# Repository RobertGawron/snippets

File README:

Projects from my blog ( http://robertgawron.blogspot.com/ ).

Visit README in project directory for description and link to an article.

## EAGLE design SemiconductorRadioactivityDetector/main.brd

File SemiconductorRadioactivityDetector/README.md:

Current version located here:

https://github.com/RobertGawron/SemiconductorRadioactivityDetector

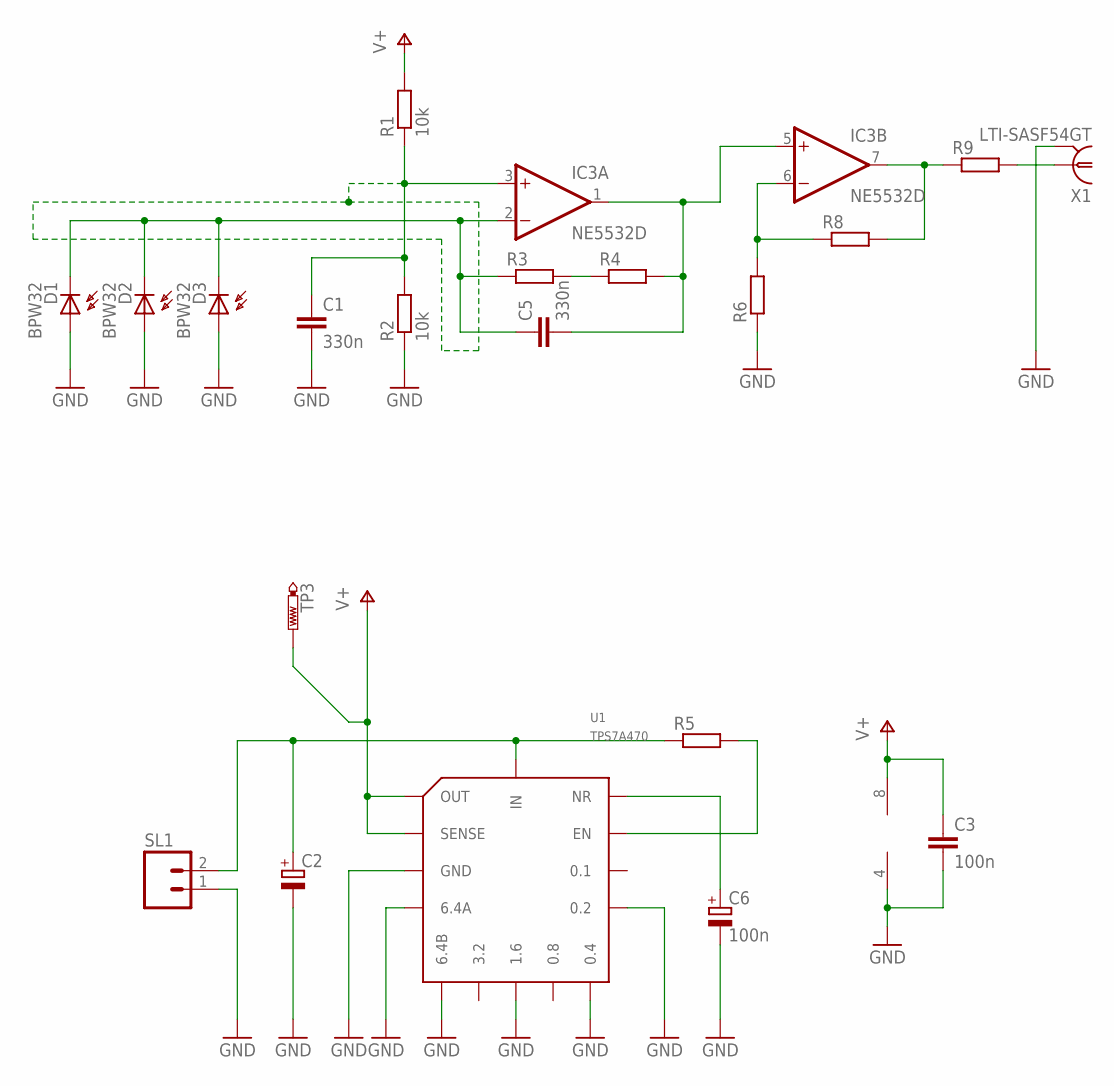
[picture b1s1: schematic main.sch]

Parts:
C1, C5: 330n; C0805
C2: CPOL-EUT/3528-12R; T/3528-12R
C3: 100n; C0805
C6: 100n; A/3216-18W
D1, D2, D3: BPW32
IC3: NE5532D; SO08
R1, R2: 10k; R0805
R3, R4: R-EU_MELF0204W; MINI_MELF-0204W
R5: R-EU_M1206; M1206
R6, R9: R-EU_0204/2V; 0204V
R8: R-EU_M0805; M0805
SL1: M02; 02P
TP3: PTR1TP12R; TP12R
U1: TPS7A470; S-PVQFN-N20
X1: LTI-SASF54GT

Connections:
GND: C1.2, C2.-, C3.2, C6.-, D1.A, D2.A, D3.A, IC3.4 (V-), R2.1, R6.1, SL1.1, U1.2 (GND), U1.4 (6.4A), U1.5 (6.4B), U1.7 (GND), U1.8 (1.6), U1.10 (0.4), U1.11 (0.2), U1.17 (GND), U1.18 (GND), U1.19 (GND), U1.EXP (GND), X1.2, X1.3 (2), X1.4 (2), X1.5 (2)
unnamed: C5.2, IC3.1 (OUT), IC3.5 (+IN), R4.2
unnamed: IC3.6 (-IN), R6.2, R8.1
unnamed: R3.2, R4.1
unnamed: C5.1, D1.K (C), D2.K (C), D3.K (C), IC3.2 (-IN), R3.1
unnamed: C6.+, U1.14 (NR)
unnamed: R5.2, U1.13 (EN)
unnamed: C2.+, R5.1, SL1.2, U1.15 (IN), U1.16 (IN)
unnamed: IC3.7 (OUT), R8.2, R9.1
unnamed: C1.1, IC3.3 (+IN), R1.1, R2.2
unnamed: R9.2, X1.1
V+: C3.1, IC3.8 (V+), R1.2, TP3.TP, U1.1 (OUT), U1.3 (SENSE), U1.20 (OUT)

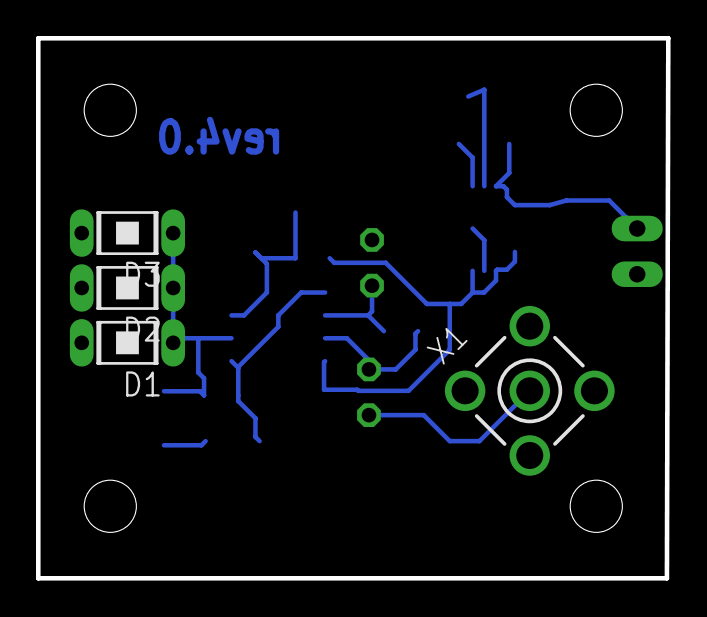
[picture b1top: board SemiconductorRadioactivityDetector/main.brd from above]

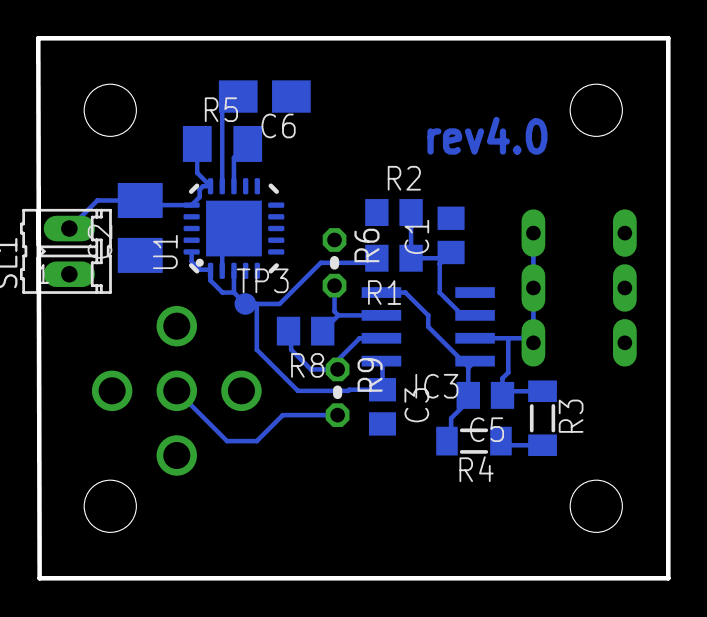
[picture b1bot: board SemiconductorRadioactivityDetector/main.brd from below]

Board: 2 copper layers, 35.0 x 30.0 mm, 21 parts (17 on the bottom side), 12 nets.

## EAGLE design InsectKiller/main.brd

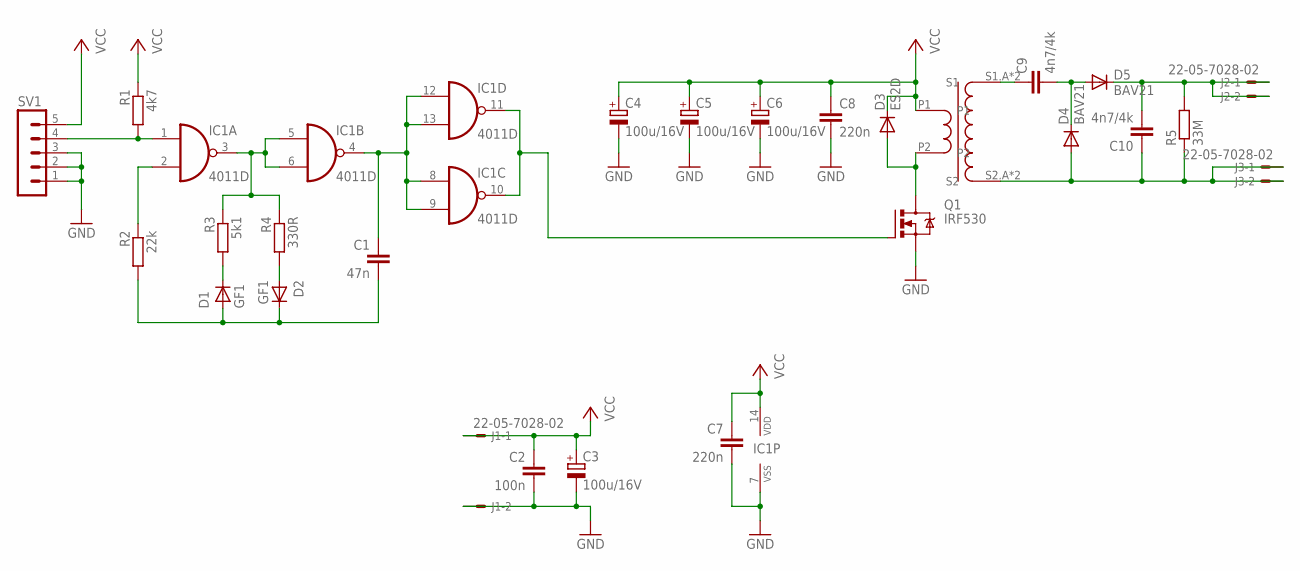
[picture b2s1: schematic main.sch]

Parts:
11: CCFL_INVERTER_COIL
C1: 47n; C025-025X050
C2: 100n; C0805
C3, C4, C5, C6: 100u/16V; 153CLV-0505
C7, C8: 220n; C0805
C9, C10: 4n7/4k; C075-042X103
D1, D2: GF1; SMA-DO214AC
D3: ES2D; SMB
D4, D5: BAV21; DO35-10
IC1: 4011D; SO14
J1, J2, J3: 22-05-7028-02; 7395-02
Q1: IRF530; TO220BV
R1: 4k7; M0805
R2: 22k; M0805
R3: 5k1; M0805
R4: 330R; M0805
R5: 33M; 0207/10
SV1: MA05-1

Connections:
GND: C2.2, C3.-, C4.-, C5.-, C6.-, C7.2, C8.2, IC1.7 (VSS), J1.2, Q1.S, SV1.1, SV1.2, SV1.3
unnamed: IC1.2 (I1), R2.1
unnamed: IC1.1 (I0), R1.2, SV1.4
unnamed: 11.P2, D3.A, Q1.D
unnamed: IC1.10 (O), IC1.11 (O), Q1.G
unnamed: C1.1, IC1.4 (O), IC1.8 (I0), IC1.9 (I1), IC1.12 (I0), IC1.13 (I1)
unnamed: 11.S1.A (S1), 11.S1.B (S1), C9.1
unnamed: C9.2, D4.C, D5.A
unnamed: C10.2, D5.C, J2.1, J2.2, R5.2
unnamed: 11.S2.A (S2), 11.S2.B (S2), C10.1, D4.A, J3.1, J3.2, R5.1
unnamed: IC1.3 (O), IC1.5 (I0), IC1.6 (I1), R3.1, R4.1
unnamed: C1.2, D1.A, D2.K (C), R2.2
unnamed: D1.K (C), R3.2
unnamed: D2.A, R4.2
VCC: 11.P1, C2.1, C3.+, C4.+, C5.+, C6.+, C7.1, C8.1, D3.C, IC1.14 (VDD), J1.1, R1.1, SV1.5

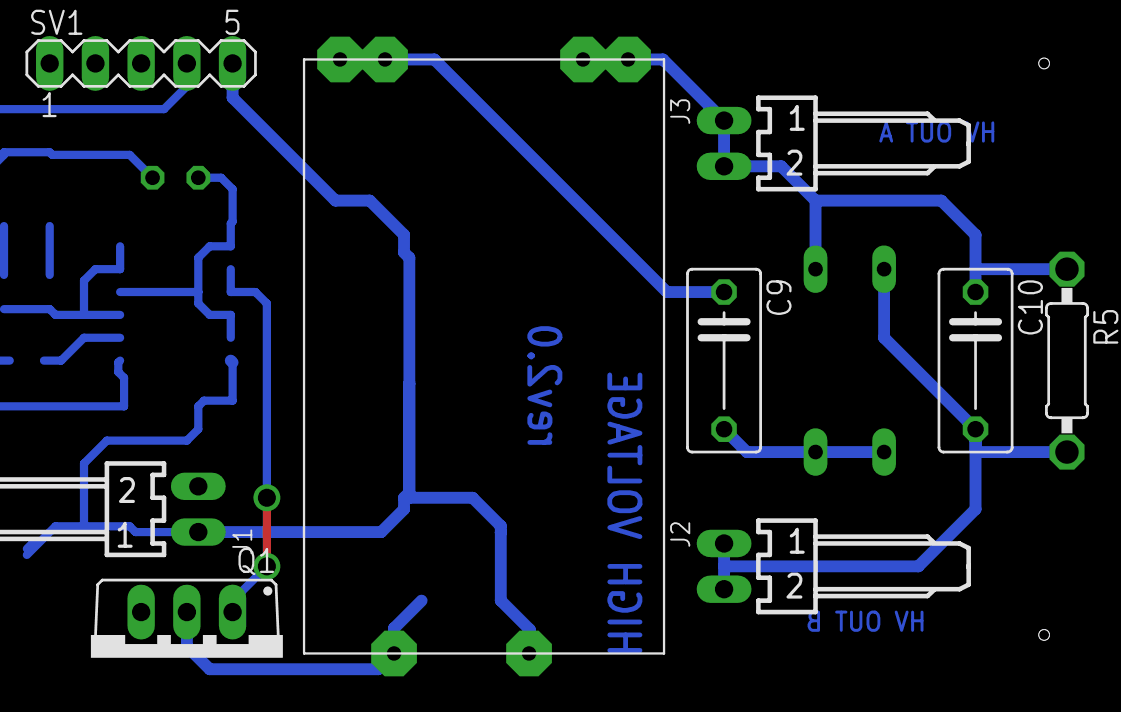
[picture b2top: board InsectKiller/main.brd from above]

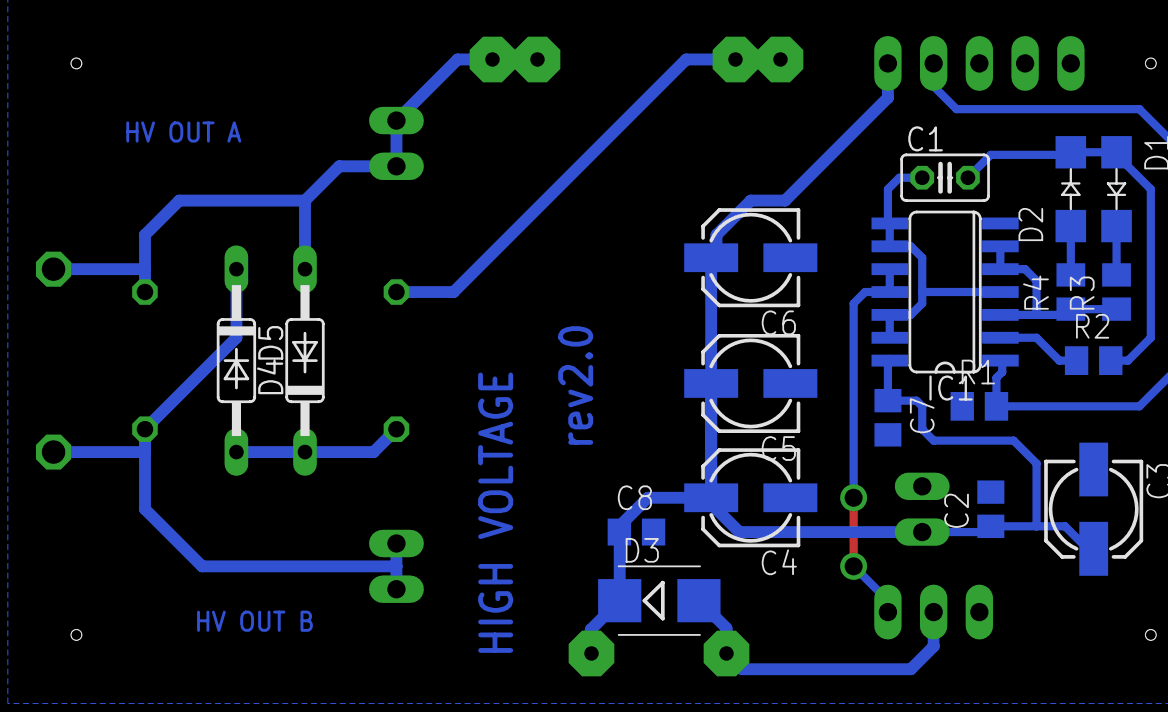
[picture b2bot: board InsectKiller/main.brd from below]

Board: 2 copper layers, 27 parts (18 on the bottom side), 15 nets.

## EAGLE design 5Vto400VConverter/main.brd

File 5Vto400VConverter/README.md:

# A small and cheap 5V/400V DC/DC converter.

For more info please visit full article:
http://robertgawron.blogspot.com/2016/03/5v400v-dcdc-converter.html

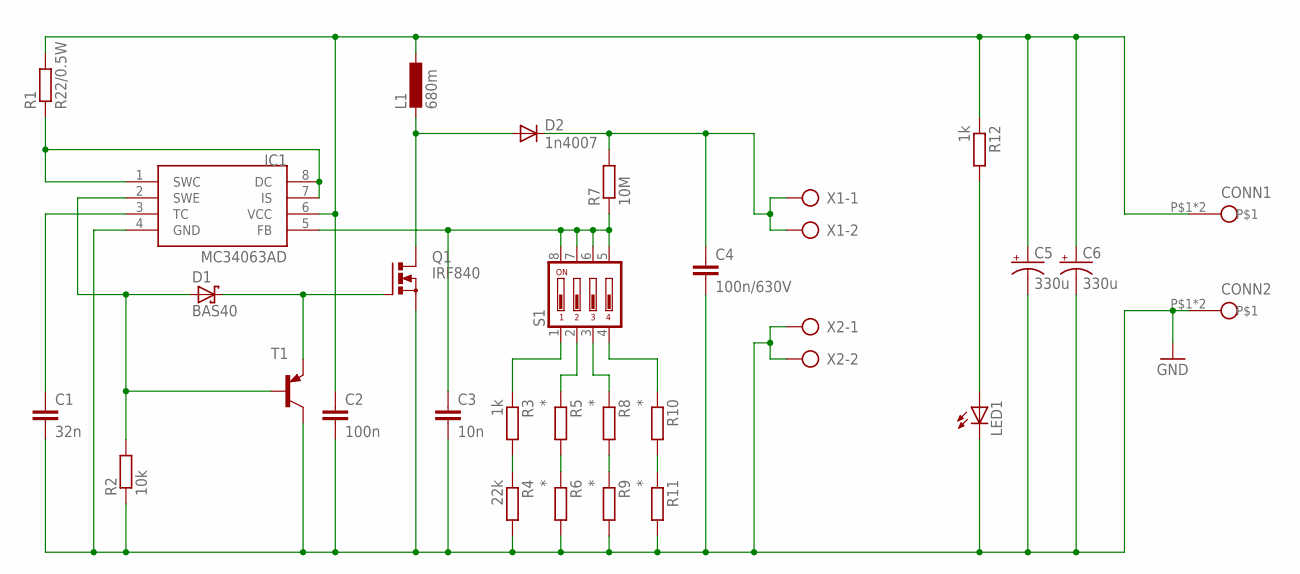
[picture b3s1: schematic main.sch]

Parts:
11, 12: BANANA-PLUG-2-PADS
C1: 32n; C025-025X050
C2: 100n; C3216
C3: 10n; C3216
C4: 100n/630V; C102-064X133
C5, C6: 330u; A/3216-18W
D1: BAS40; SOT23
D2: 1n4007; DO41-10
IC1: MC34063AD; SOIC8
L1: 680m; 0207/5V
LED1: LED3MM
Q1: IRF840; TO220BV
R1: R22/0.5W; 0207/5V
R2: 10k; R1206
R3, R12: 1k; R1206
R4: 22k; R1206
R5, R6, R8, R9, R10, R11: *; R1206
R7: 10M; 0207/5V
S1: DS04; DS-04
T1: BC807-40-PNP-SOT23-BEC; SOT23-BEC
X1, X2: AK500/2-H

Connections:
GND: 12.P$1, 12.P$2, C1.2, C2.2, C3.2, C4.2, C5.-, C6.-, IC1.4 (GND), LED1.K (C), Q1.S, R2.1, R4.2, R6.2, R9.2, R11.2, T1.C, X2.1, X2.2
unnamed: R8.2, R9.1
unnamed: R5.2, R6.1
unnamed: R3.2, R4.1
unnamed: R10.2, R11.1
unnamed: C1.1, IC1.3 (TC)
unnamed: R3.1, S1.1
unnamed: R5.1, S1.2
unnamed: R8.1, S1.3
unnamed: R10.1, S1.4
unnamed: LED1.A, R12.2
unnamed: IC1.1 (SWC), IC1.7 (IS), IC1.8 (DC), R1.1
unnamed: C3.1, IC1.5 (FB), R7.1, S1.5, S1.6, S1.7, S1.8
unnamed: D1.1 (A), IC1.2 (SWE), R2.2, T1.B
unnamed: D2.A, L1.2, Q1.D
unnamed: D1.3 (C), Q1.G, T1.E
unnamed: C4.1, D2.C, R7.2, X1.1, X1.2
VCC: 11.P$1, 11.P$2, C2.1, C5.+, C6.+, IC1.6 (VCC), L1.1, R1.2, R12.1

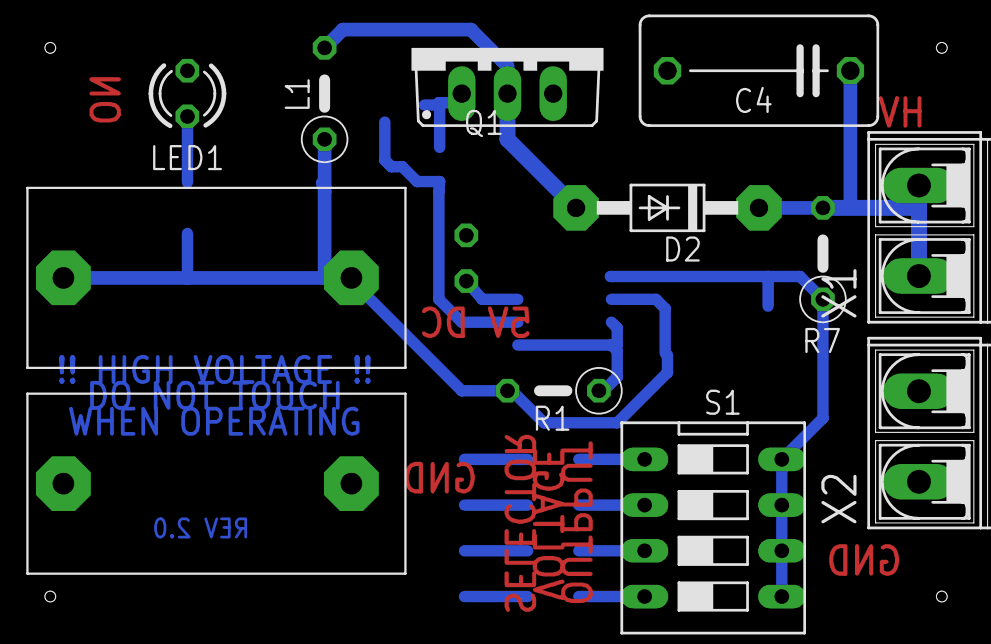
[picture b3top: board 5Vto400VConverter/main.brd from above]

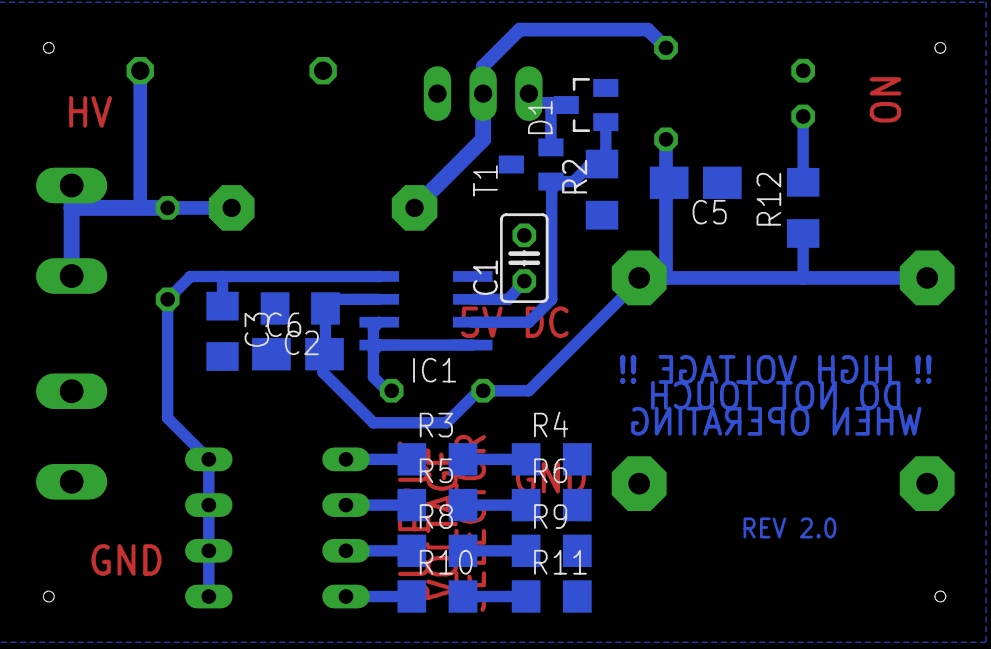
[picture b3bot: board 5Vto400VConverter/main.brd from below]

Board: 2 copper layers, 30 parts (18 on the bottom side), 18 nets.

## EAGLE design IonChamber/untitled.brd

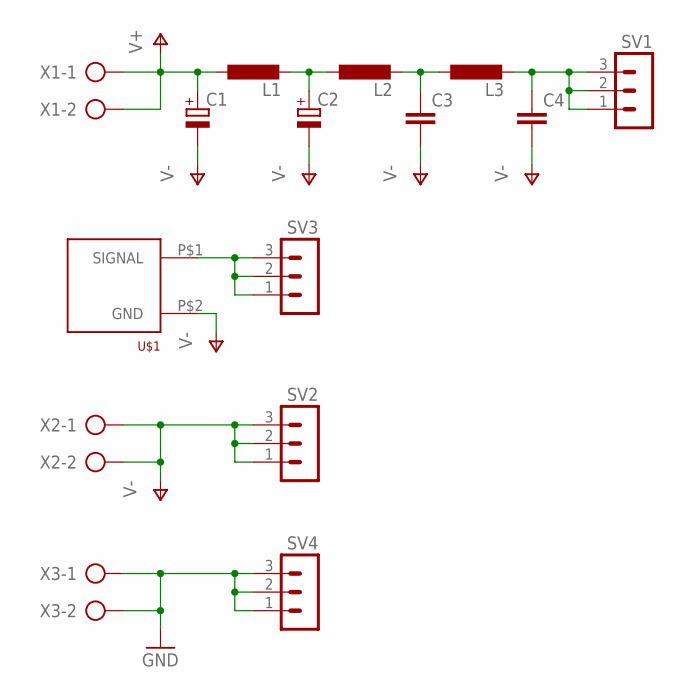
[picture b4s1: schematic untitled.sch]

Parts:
C1, C2: CPOL-EUSMCA; SMC_A
C3, C4: C-EUC1206; C1206
L1: L-EU0204/7; 0204/7
L2, L3: L-EUL1812; L1812
SV1, SV2, SV3, SV4: MA03-1
U$1: BNC_VERTICAL
X1, X2, X3: AK500/2-H

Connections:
GND: SV4.1, SV4.2, SV4.3, X3.1, X3.2
unnamed: C4.1, L3.2, SV1.1, SV1.2, SV1.3
unnamed: C2.+, L1.2, L2.1
unnamed: SV3.1, SV3.2, SV3.3, U$1.P$1 (SIGNAL)
unnamed: C3.1, L2.2, L3.1
V+: C1.+, L1.1, X1.1, X1.2
V-: C1.-, C2.-, C3.2, C4.2, SV2.1, SV2.2, SV2.3, U$1.P$2 (GND), X2.1, X2.2

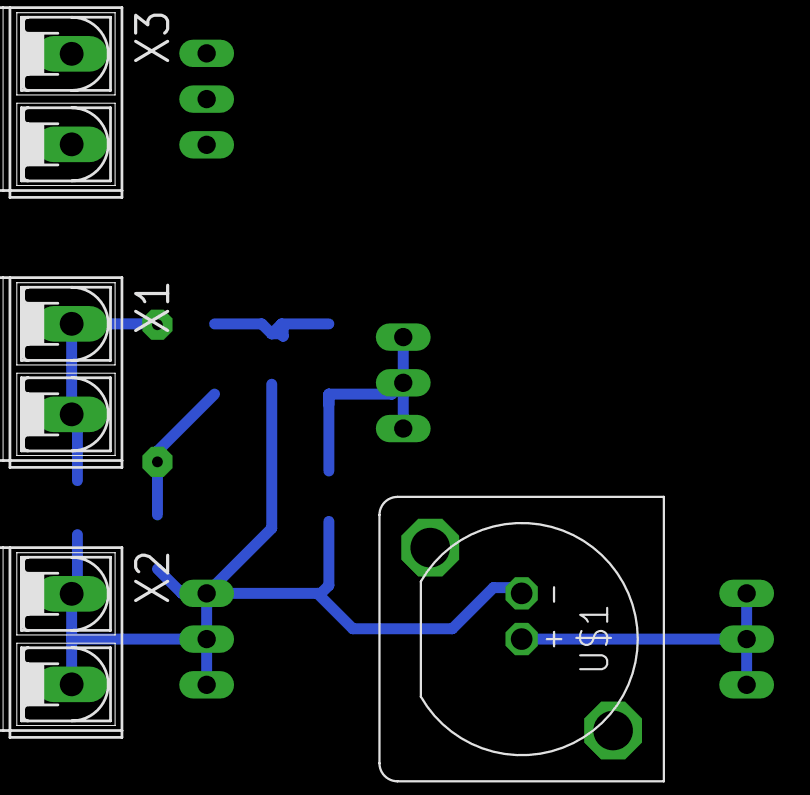
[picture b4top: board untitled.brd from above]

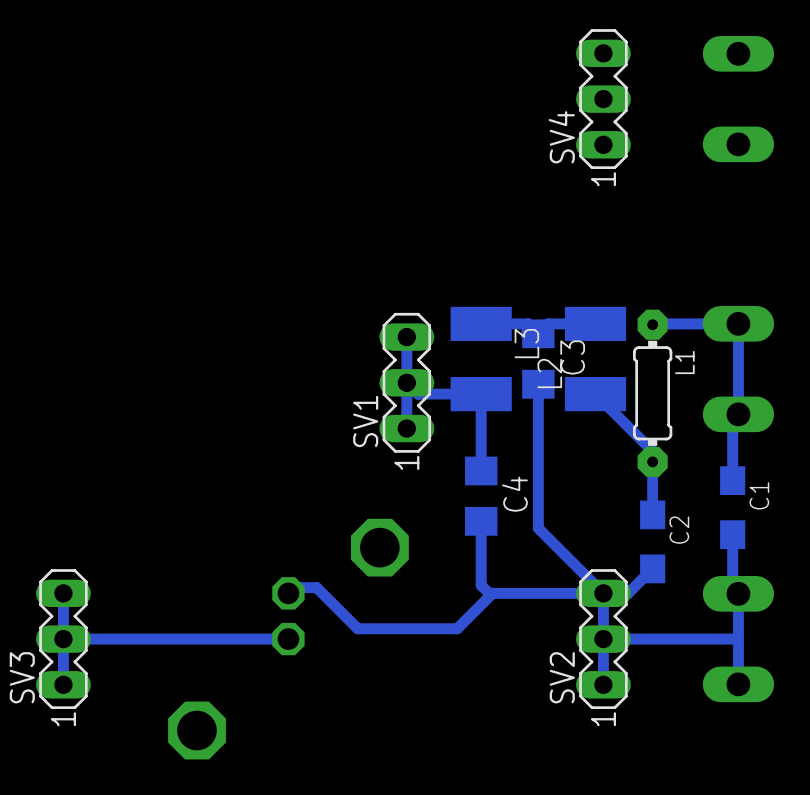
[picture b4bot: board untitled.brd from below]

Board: 2 copper layers, 15 parts (11 on the bottom side), 7 nets.

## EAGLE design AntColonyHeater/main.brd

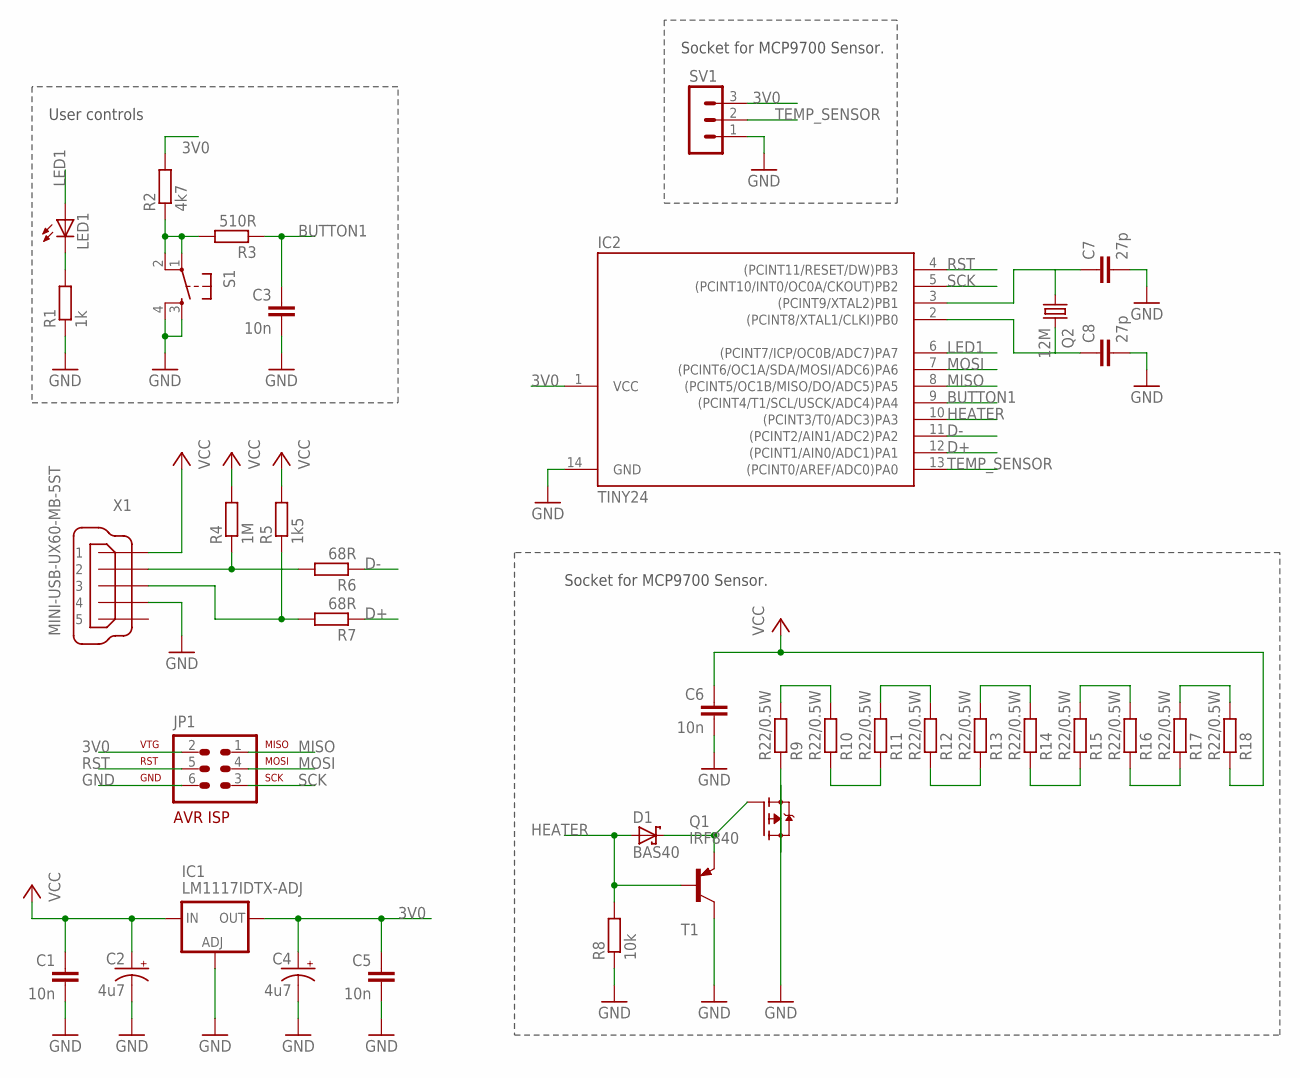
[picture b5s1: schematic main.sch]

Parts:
C1, C3, C5, C6: 10n; C1206
C2, C4: 4u7; A/3216-18W
C7, C8: 27p; C025-024X044
D1: BAS40; SOT23
IC1: LM1117IDTX-ADJ; TO252
IC2: TINY24; DIL14
JP1: AVR-ISP-6
LED1: LEDCHIP-LED0805; CHIP-LED0805
Q1: IRF840; TO252
Q2: 12M; HC18U-V
R1: 1k; R1206
R2: 4k7; R1206
R3: 510R; R1206
R4: 1M; R1206
R5: 1k5; R1206
R6, R7: 68R; R1206
R8: 10k; R1206
R9, R10, R11, R12, R13, R14, R15, R16, R17, R18: R22/0.5W; 0207/12
S1: TAC_SWITCHPTH; TACTILE-PTH
SV1: MA03-1
T1: BC807-40-PNP-SOT23-BEC; SOT23-BEC
X1: MINI-USB-UX60-MB-5ST; UX60-MB-5ST

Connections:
3V0: C4.+, C5.1, IC1.TAB (OUT), IC2.1 (VCC), JP1.2, R2.2, SV1.3
BUTTON1: C3.1, IC2.9 ((PCINT4/T1/SCL/USCK/ADC4)PA4), R3.1
D+: IC2.12 ((PCINT1/AIN0/ADC1)PA1), R7.1
D-: IC2.11 ((PCINT2/AIN1/ADC2)PA2), R6.1
GND: C1.2, C2.-, C3.2, C4.-, C5.2, C6.2, C7.2, C8.2, IC1.1 (ADJ), IC2.14 (GND), JP1.6, Q1.2 (S), R1.1, R8.1, S1.3, S1.4, SV1.1, T1.C, X1.4
HEATER: D1.1 (A), IC2.10 ((PCINT3/T0/ADC3)PA3), R8.2, T1.B
LED1: IC2.6 ((PCINT7/ICP/OC0B/ADC7)PA7), LED1.A
MISO: IC2.8 ((PCINT5/OC1B/MISO/DO/ADC5)PA5), JP1.1
MOSI: IC2.7 ((PCINT6/OC1A/SDA/MOSI/ADC6)PA6), JP1.4
unnamed: R4.1, R6.2, X1.2
unnamed: Q1.3 (D), R9.1
unnamed: R5.1, R7.2, X1.3
unnamed: C7.1, IC2.3 ((PCINT9/XTAL2)PB1), Q2.1
unnamed: R9.2, R10.2
unnamed: R2.1, R3.2, S1.1, S1.2
unnamed: R10.1, R11.1
unnamed: R11.2, R12.2
unnamed: R12.1, R13.1
unnamed: R13.2, R14.2
unnamed: R14.1, R15.1
unnamed: R15.2, R16.2
unnamed: R16.1, R17.1
unnamed: LED1.C, R1.2
unnamed: D1.3 (C), Q1.1 (G), T1.E
unnamed: R17.2, R18.2
PB0: C8.1, IC2.2 ((PCINT8/XTAL1/CLKI)PB0), Q2.2
RST: IC2.4 ((PCINT11/RESET/DW)PB3), JP1.5
SCK: IC2.5 ((PCINT10/INT0/OC0A/CKOUT)PB2), JP1.3
TEMP_SENSOR: IC2.13 ((PCINT0/AREF/ADC0)PA0), SV1.2
VCC: C1.1, C2.+, C6.1, IC1.2 (IN), R4.2, R5.2, R18.1, X1.1

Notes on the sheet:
Socket for MCP9700 Sensor.
User controls

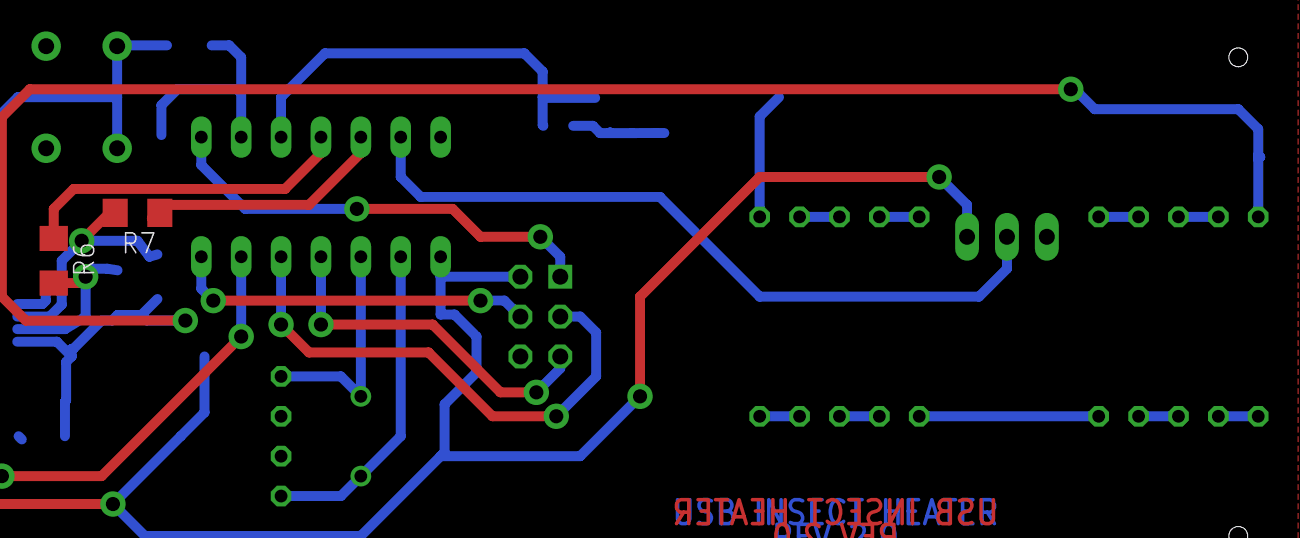
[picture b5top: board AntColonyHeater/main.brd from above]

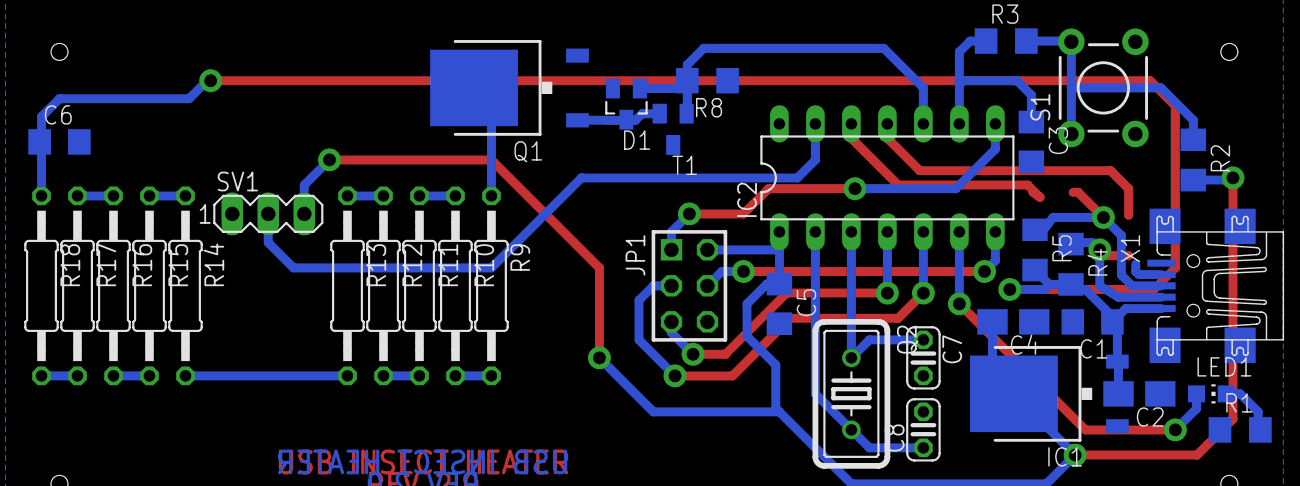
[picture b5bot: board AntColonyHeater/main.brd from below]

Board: 2 copper layers, 37 parts (35 on the bottom side), 30 nets.

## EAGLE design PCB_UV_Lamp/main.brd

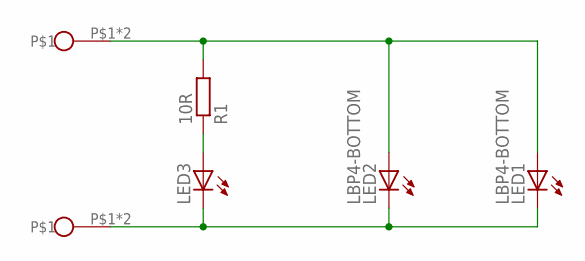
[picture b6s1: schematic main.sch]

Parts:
GND: BANANA-PLUG-2-PADS
LED1, LED2: LBP4-BOTTOM; P47F-BOTTOM
LED3: LED3MM
R1: 10R; R1206
U$1: BANANA-PLUG-2-PADS

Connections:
GND: LED1.A, LED2.A, R1.2, U$1.P$1, U$1.P$2
unnamed: GND.P$1, GND.P$2, LED1.C, LED2.C, LED3.K (C)
unnamed: LED3.A, R1.1

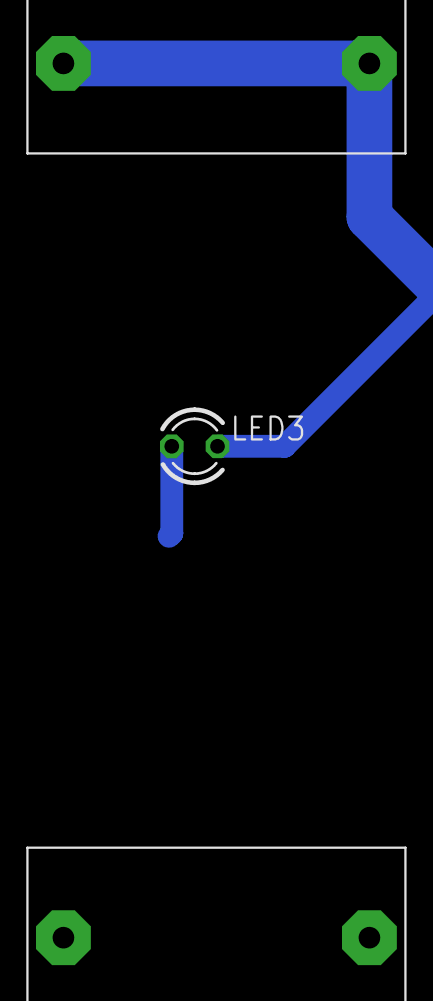
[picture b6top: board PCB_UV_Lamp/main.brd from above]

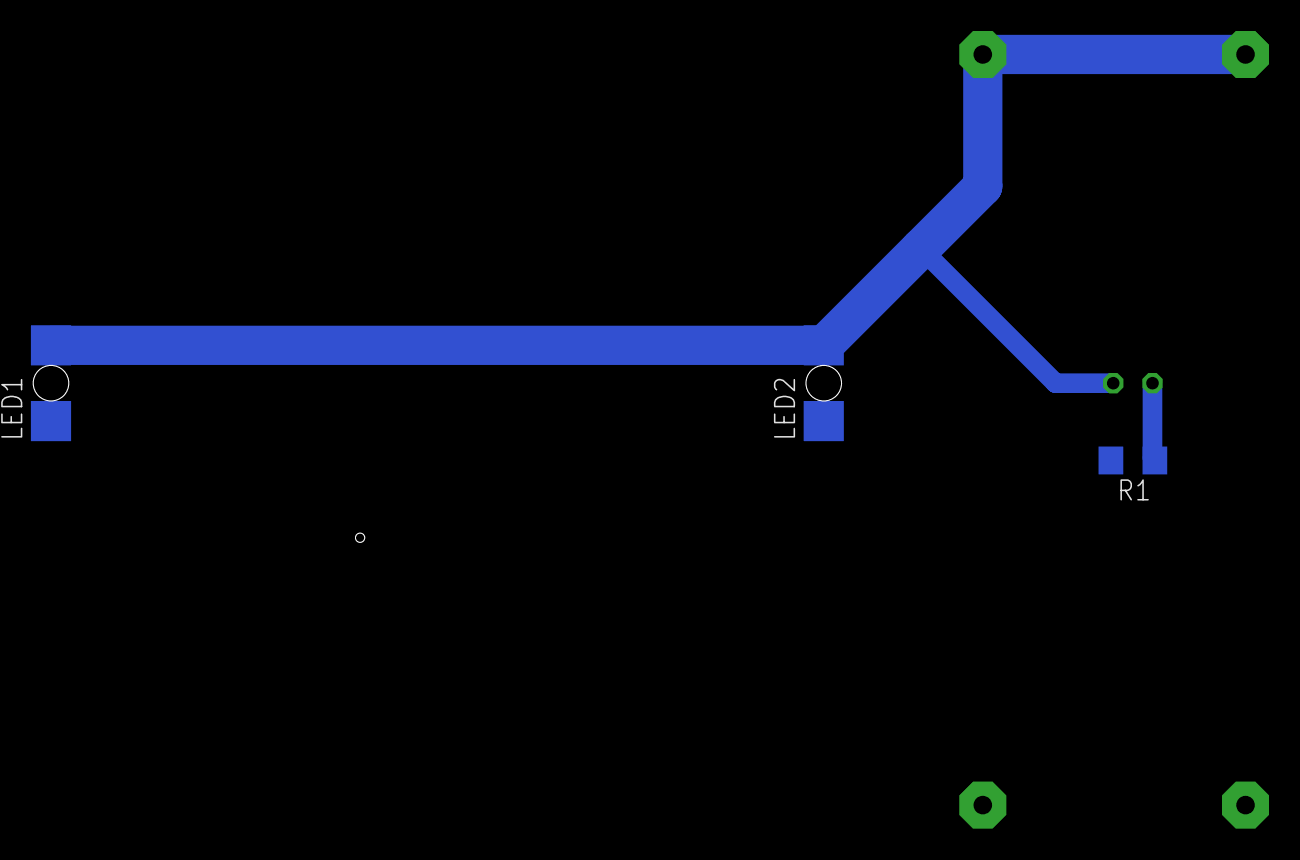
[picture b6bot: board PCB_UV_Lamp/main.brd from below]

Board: 2 copper layers, 6 parts (3 on the bottom side), 3 nets.

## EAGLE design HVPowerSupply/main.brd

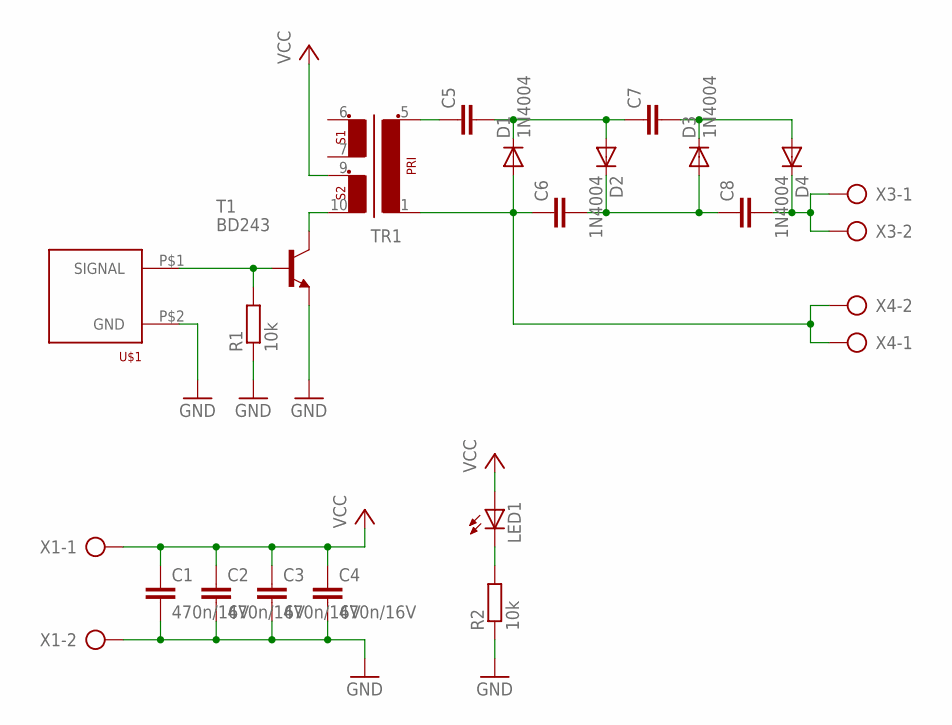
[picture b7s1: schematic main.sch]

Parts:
C1, C2, C3, C4: 470n/16V; C025-025X050
C5, C6, C7, C8: C-EU150-064X183; C150-064X183
D1, D2, D3, D4: 1N4004; DO41-10
LED1: LED3MM
R1, R2: 10k; M1206
T1: BD243; TO220
TR1: EI30-2
U$1: BNC_VERTICAL
X1, X3, X4: AK500/2-H

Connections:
GND: C1.2, C2.2, C3.2, C4.2, R1.1, R2.1, T1.3 (E), U$1.P$2 (GND), X1.2
unnamed: C6.1, D1.A, TR1.1, X4.1, X4.2
unnamed: C5.2, C7.1, D1.C, D2.A
unnamed: C6.2, C8.1, D2.C, D3.A
unnamed: C7.2, D3.C, D4.A
unnamed: C8.2, D4.C, X3.1, X3.2
unnamed: C5.1, TR1.5 (2)
unnamed: T1.2 (C), TR1.10 (6)
unnamed: LED1.K (C), R2.2
unnamed: R1.2, T1.1 (B), U$1.P$1 (SIGNAL)
VCC: C1.1, C2.1, C3.1, C4.1, LED1.A, TR1.9 (5), X1.1

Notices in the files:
parts and their libraries:
SparkFun: Licensing: CC v3.0 Share-Alike You are welcome to use this library for commercial purposes.
